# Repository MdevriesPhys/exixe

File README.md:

# exixe: Low-cost miniature Nixie tube driver modules

[Get exixe](https://www.tindie.com/products/dekuNukem/exixe-miniture-nixie-tube-driver-modules/) | [User manual](getting_started.md)

Forked from original dekuNukem repo, some modifications to boards and firmware.

exixe is a miniature driver module for IN-12 and IN-14 Nixie tubes.

It aims to simplify Nixie tube related projects by eliminating the need for obscure vintage driver chips and multiplexing circuits. Instead, you can control every digit and the RGB backlight via SPI using only 3 wires and 1 line of code.

exixe is cheap, small and modular for easy integration. It is compatible with Arduino, Raspberry Pi, and virtually all embedded dev boards today.

## Updated firmware 2026-03-03
Original firmware for IN-14 boards had an issue where the LEDs would be slightly on when set to 0 brightness. This has been updating in exixie14.hex firmware. See [Getting started](getting_started.md) for information about reflashing.

## Buy exixe on Tindie!

I did a small production run of exixe modules, and now you can buy them directly on Tindie:

https://www.tindie.com/products/dekuNukem/exixe-miniture-nixie-tube-driver-modules/

## Features

Compared to the traditional approach, exixe modules offers significant advantages:

#### Small and modular
* 2x4 cm (0.79x1.57 inches)
* Breadboard friendly
* Easy integration
* Reusable

#### SPI interface
* High speed, up to 24MHz SCLK
* Simple 16-byte command packet
* Available on virtually all embedded systems including Arduino and Raspberry Pi

#### Advanced control
* RGB backlight
* 128 brightness levels
* Hardware PWM on all cathodes and LEDs for smooth dimming and animations

#### Tube overdrive
* Optionally allows twice the cathode current
* For poisoned cathodes in second-hand tubes
* [Before](resources/no_overdrive.jpg) and [after](resources/with_overdrive.jpg).

#### No multiplexing
* Brighter display
* Longer tube life
* Simpler design
* Lower power consumption

## Getting started

Please see [getting_started.md](/getting_started.md)

## Arduino Library

Please [click here](arduino_library)

## Raspberry Pi/Python Library

Please [click here](python_library)

## Pinout, SPI command format and technical details

Please see [technical_details.md](/technical_details.md)

## Supported tubes

exixe-14 module is primarily designed for IN-14 Nixie tubes, but will also work with IN-16 and IN-19 tubes. IN-19 specific board in development.

exixe-12 module is primarily designed for IN-12 Nixie tubes, but works with IN-15 tubes as well.

## Using other tubes

You can also use exixe module with unsupported tubes, with some modification.

Please see [unsupported_tubes.md](/unsupported_tubes.md)

## Making some yourself

Please see [making_some.md](/making_some.md)

## Contact

Questions? Feel free to [open an issue](https://github.com/dekuNukem/exixe/issues). This is the preferred way since it helps other people too.

You can also email me at `dekunukem gmail com` for inquires.

## More photos

exixe-12 working with an Arduino Micro, showing a smooth crossfade animation:

exixe-14 in action on a [finished clock](https://github.com/dekuNukem/exixe_clock):

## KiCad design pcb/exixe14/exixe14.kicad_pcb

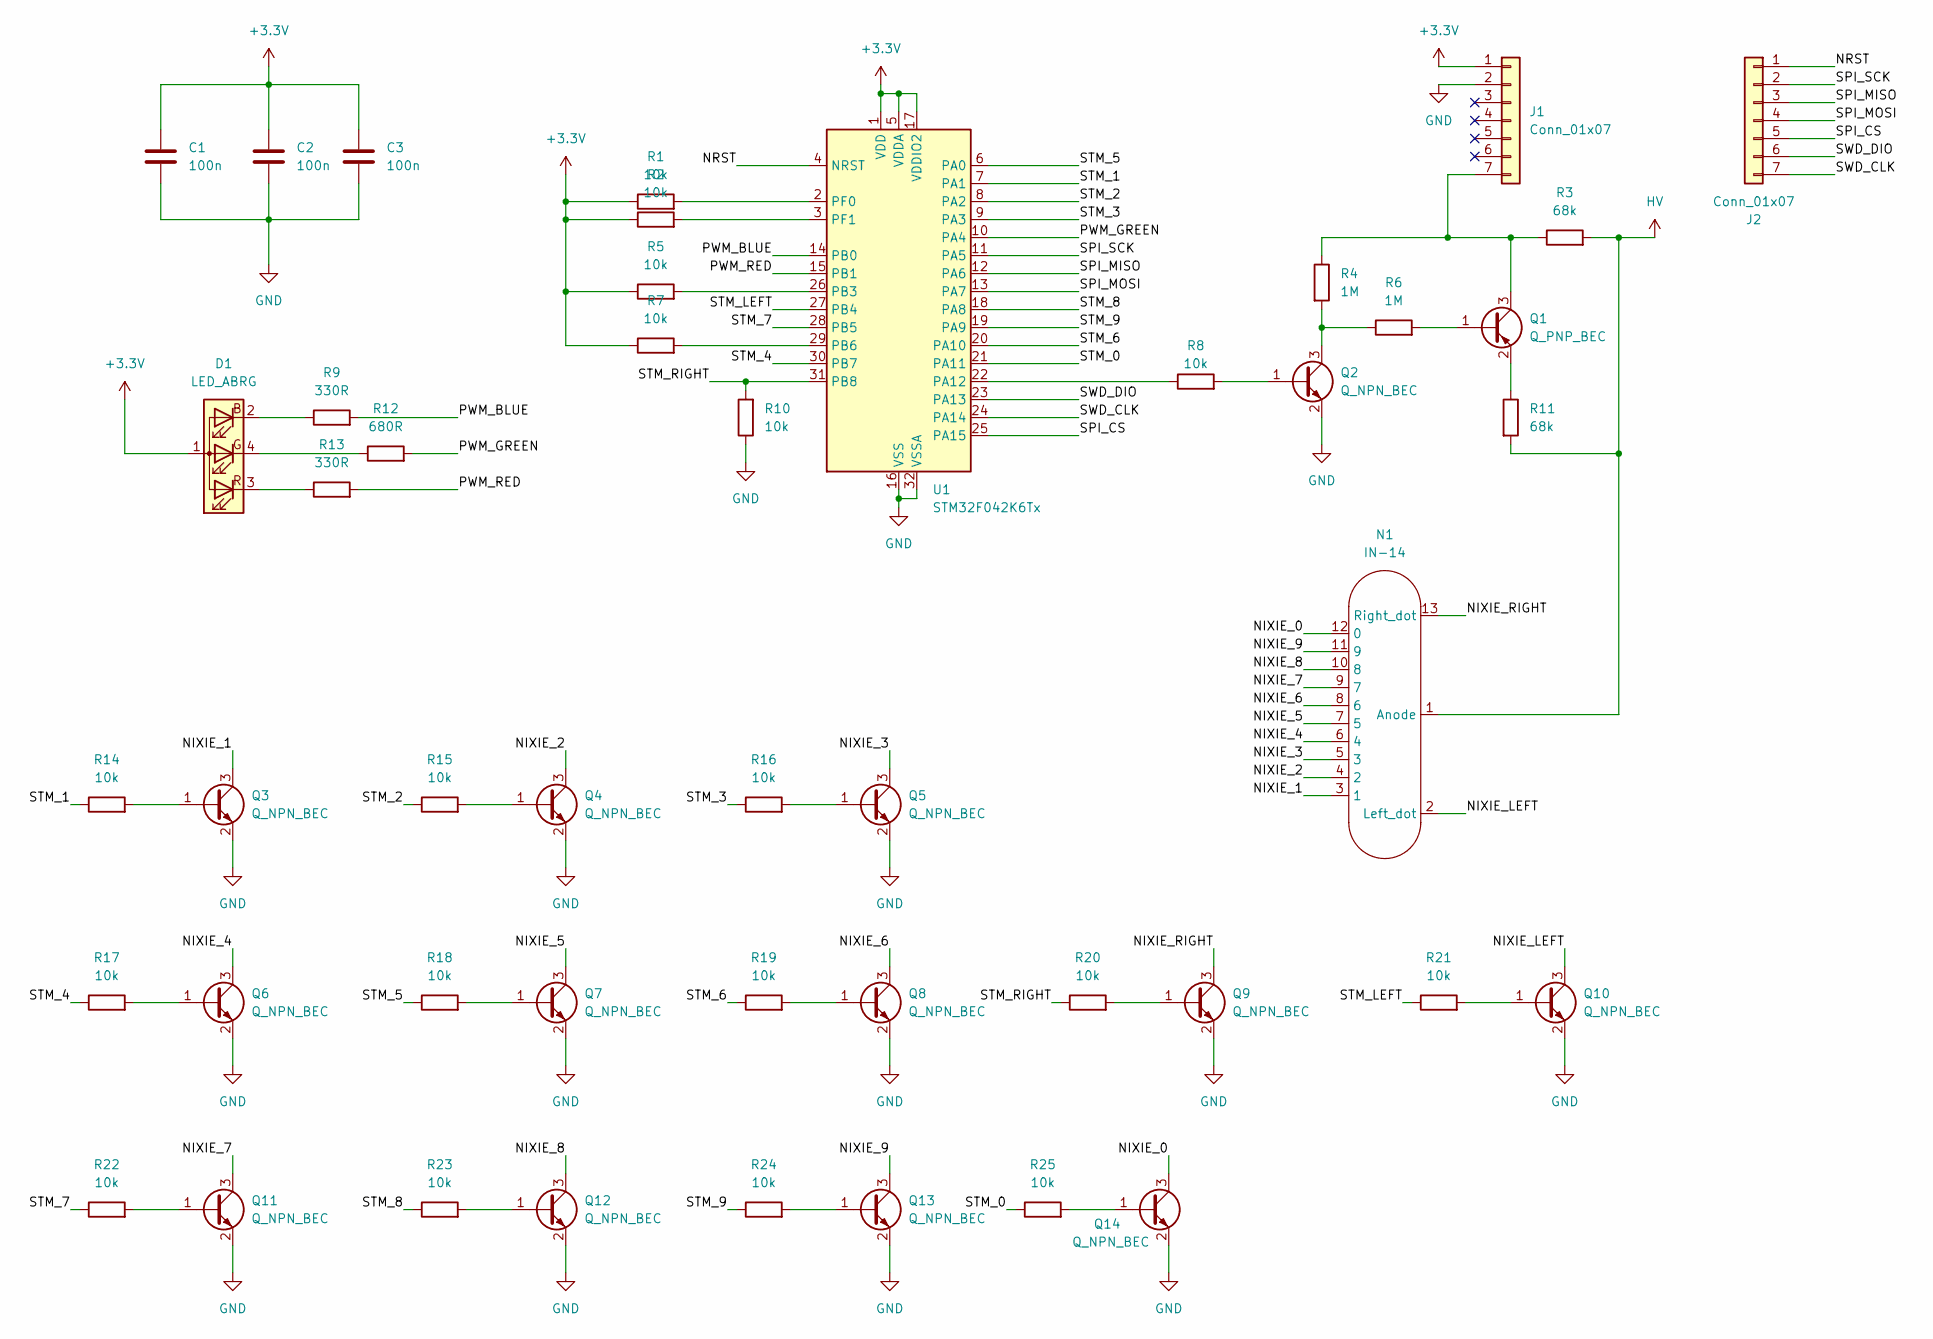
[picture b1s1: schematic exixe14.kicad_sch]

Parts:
C1, C2, C3: 100n; C_0805_2012Metric
D1: LED_ABRG; LED_RGB_Wuerth-PLCC4_3.2x2.8mm_150141M173100
J1, J2: Conn_01x07; PinHeader_1x07_P2.54mm_Vertical
N1: IN-14
Q1: Q_PNP_BEC; SOT-323_SC-70
Q2, Q3, Q4, Q5, Q6, Q7, Q8, Q9, Q10, Q11, Q12, Q13, Q14: Q_NPN_BEC; SOT-323_SC-70
R1, R2, R5, R7, R8, R10, R14, R15, R16, R17, R18, R19, R20, R21, R22, R23, R24, R25: 10k; R_0805_2012Metric
R3, R11: 68k; R_0805_2012Metric
R4, R6: 1M; R_0805_2012Metric
R9, R13: 330R; R_0805_2012Metric
R12: 680R; R_0805_2012Metric
U1: STM32F042K6Tx; LQFP-32_7x7mm_P0.8mm

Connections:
+3.3V: C1.1, C2.1, C3.1, D1.1 (A), J1.1, R1.1, R2.1, R5.1, R7.1, U1.1 (VDD), U1.5 (VDDA), U1.17 (VDDIO2)
/NIXIE_0: N1.12 (0), Q14.3 (C)
/NIXIE_1: N1.3 (1), Q3.3 (C)
/NIXIE_2: N1.4 (2), Q4.3 (C)
/NIXIE_3: N1.5 (3), Q5.3 (C)
/NIXIE_4: N1.6 (4), Q6.3 (C)
/NIXIE_5: N1.7 (5), Q7.3 (C)
/NIXIE_6: N1.8 (6), Q8.3 (C)
/NIXIE_7: N1.9 (7), Q11.3 (C)
/NIXIE_8: N1.10 (8), Q12.3 (C)
/NIXIE_9: N1.11 (9), Q13.3 (C)
/NIXIE_LEFT: N1.2 (Left_dot), Q10.3 (C)
/NIXIE_RIGHT: N1.13 (Right_dot), Q9.3 (C)
/NRST: J2.1, U1.4 (NRST)
/PWM_BLUE: R9.2, U1.14 (PB0)
/PWM_GREEN: R12.2, U1.10 (PA4)
/PWM_RED: R13.2, U1.15 (PB1)
/SPI_CS: J2.5, U1.25 (PA15)
/SPI_MISO: J2.3, U1.12 (PA6)
/SPI_MOSI: J2.4, U1.13 (PA7)
/SPI_SCK: J2.2, U1.11 (PA5)
/STM_0: R25.1, U1.21 (PA11)
/STM_1: R14.1, U1.7 (PA1)
/STM_2: R15.1, U1.8 (PA2)
/STM_3: R16.1, U1.9 (PA3)
/STM_4: R17.1, U1.30 (PB7)
/STM_5: R18.1, U1.6 (PA0)
/STM_6: R19.1, U1.20 (PA10)
/STM_7: R22.1, U1.28 (PB5)
/STM_8: R23.1, U1.18 (PA8)
/STM_9: R24.1, U1.19 (PA9)
/STM_LEFT: R21.1, U1.27 (PB4)
/STM_RIGHT: R10.2, R20.1, U1.31 (PB8)
/SWD_CLK: J2.7, U1.24 (PA14)
/SWD_DIO: J2.6, U1.23 (PA13)
GND: C1.2, C2.2, C3.2, J1.2, Q2.2 (E), Q3.2 (E), Q4.2 (E), Q5.2 (E), Q6.2 (E), Q7.2 (E), Q8.2 (E), Q9.2 (E), Q10.2 (E), Q11.2 (E), Q12.2 (E), Q13.2 (E), Q14.2 (E), R10.1, U1.16 (VSS), U1.32 (VSSA)
HV: N1.1 (Anode), R3.2, R11.2
unnamed: D1.2 (BK), R9.1
unnamed: D1.4 (GK), R12.1
unnamed: D1.3 (RK), R13.1
unnamed: J1.7, Q1.3 (C), R3.1, R4.1
unnamed: Q1.1 (B), R6.2
unnamed: Q1.2 (E), R11.1
unnamed: Q2.1 (B), R8.2
unnamed: Q2.3 (C), R4.2, R6.1
unnamed: Q3.1 (B), R14.2
unnamed: Q4.1 (B), R15.2
unnamed: Q5.1 (B), R16.2
unnamed: Q6.1 (B), R17.2
unnamed: Q7.1 (B), R18.2
unnamed: Q8.1 (B), R19.2
unnamed: Q9.1 (B), R20.2
unnamed: Q10.1 (B), R21.2
unnamed: Q11.1 (B), R22.2
unnamed: Q12.1 (B), R23.2
unnamed: Q13.1 (B), R24.2
unnamed: Q14.1 (B), R25.2
unnamed: R8.1, U1.22 (PA12)
unnamed: R5.2, U1.26 (PB3)
unnamed: R7.2, U1.29 (PB6)
unnamed: R1.2, U1.2 (PF0)
unnamed: R2.2, U1.3 (PF1)

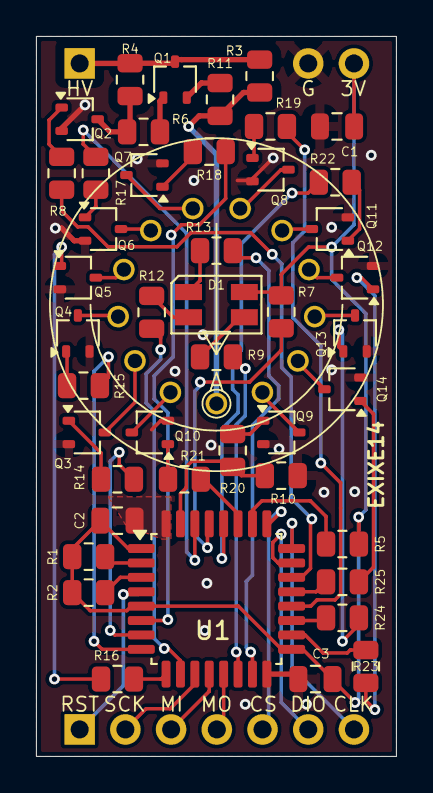
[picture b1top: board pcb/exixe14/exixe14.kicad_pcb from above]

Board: 2 copper layers, 20.0 x 40.0 mm, 47 parts (0 on the bottom side), 62 nets.

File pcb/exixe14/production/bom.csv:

Designator,Footprint,Quantity,Value,LCSC Part #
"C1, C2, C3",0805,3,100n,
D1,LED_RGB_Wuerth-PLCC4_3.2x2.8mm_150141M173100,1,LED_ABRG,
"J1, J2",PinHeader_1x07_P2.54mm_Vertical,2,Conn_01x07,
N1,IN-14,1,IN-14,
Q1,SOT-323_SC-70,1,Q_PNP_BEC,
"Q10, Q11, Q12, Q13, Q14, Q2, Q3, Q4, Q5, Q6, Q7, Q8, Q9",SOT-323_SC-70,13,Q_NPN_BEC,
"R1, R10, R14, R15, R16, R17, R18, R19, R2, R20, R21, R22, R23, R24, R25, R5, R7, R8",0805,18,10k,
"R11, R3",0805,2,68k,
R12,0805,1,680R,
"R13, R9",0805,2,330R,
"R4, R6",0805,2,1M,
U1,LQFP-32_7x7mm_P0.8mm,1,STM32F042K6Tx,

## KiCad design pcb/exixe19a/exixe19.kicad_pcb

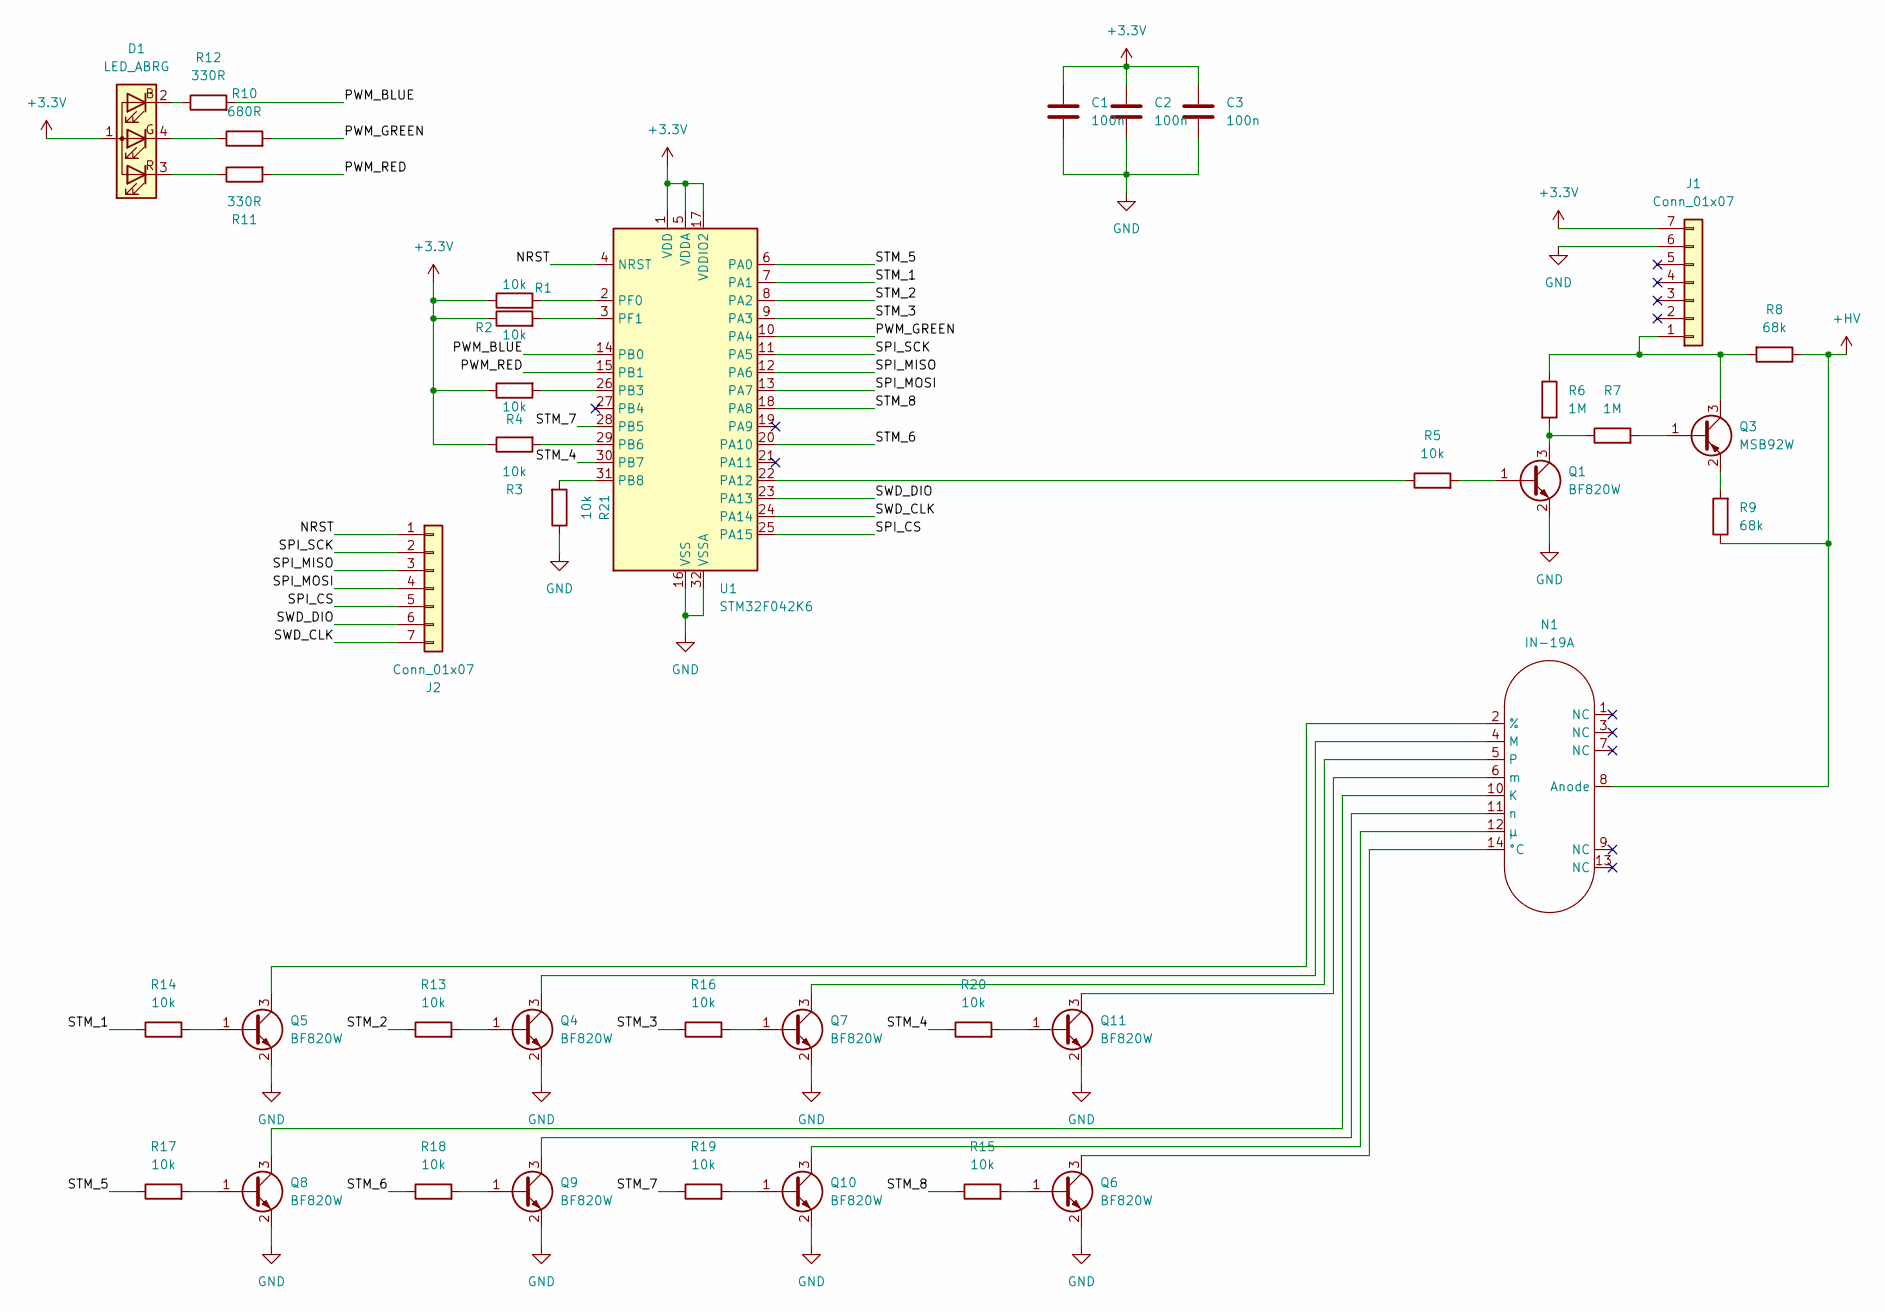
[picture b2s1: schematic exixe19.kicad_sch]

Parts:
C1, C2, C3: 100n; C_0805_2012Metric
D1: LED_ABRG; LED_RGB_Wuerth-PLCC4_3.2x2.8mm_150141M173100
J1: Conn_01x07; PinHeader_1x07_P2.54mm_Vertical_special
J2: Conn_01x07; PinHeader_1x07_P2.54mm_Vertical
N1: IN-19A
Q1, Q4, Q5, Q6, Q7, Q8, Q9, Q10, Q11: BF820W; SOT-323_SC-70
Q3: MSB92W; SOT-323_SC-70
R1, R2, R3, R4, R5, R13, R14, R15, R16, R17, R18, R19, R20, R21: 10k; R_0805_2012Metric
R6, R7: 1M; R_0805_2012Metric
R8, R9: 68k; R_0805_2012Metric
R10: 680R; R_0805_2012Metric
R11, R12: 330R; R_0805_2012Metric
U1: STM32F042K6; TQFP-32_7x7mm_P0.8mm

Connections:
+3.3V: C1.1, C2.1, C3.1, D1.1 (A), J1.7, R1.1, R2.1, R3.1, R4.1, U1.1 (VDD), U1.5 (VDDA), U1.17 (VDDIO2)
+HV: N1.8 (Anode), R8.1, R9.1
/NRST: J2.1, U1.4 (NRST)
/PWM_BLUE: R12.2, U1.14 (PB0)
/PWM_GREEN: R10.2, U1.10 (PA4)
/PWM_RED: R11.2, U1.15 (PB1)
/SPI_CS: J2.5, U1.25 (PA15)
/SPI_MISO: J2.3, U1.12 (PA6)
/SPI_MOSI: J2.4, U1.13 (PA7)
/SPI_SCK: J2.2, U1.11 (PA5)
/STM_1: R14.1, U1.7 (PA1)
/STM_2: R13.1, U1.8 (PA2)
/STM_3: R16.1, U1.9 (PA3)
/STM_4: R20.1, U1.30 (PB7)
/STM_5: R17.1, U1.6 (PA0)
/STM_6: R18.1, U1.20 (PA10)
/STM_7: R19.1, U1.28 (PB5)
/STM_8: R15.1, U1.18 (PA8)
/SWD_CLK: J2.7, U1.24 (PA14)
/SWD_DIO: J2.6, U1.23 (PA13)
GND: C1.2, C2.2, C3.2, J1.6, Q1.2 (E), Q4.2 (E), Q5.2 (E), Q6.2 (E), Q7.2 (E), Q8.2 (E), Q9.2 (E), Q10.2 (E), Q11.2 (E), R21.1, U1.16 (VSS), U1.32 (VSSA)
unnamed: D1.2 (BK), R12.1
unnamed: D1.4 (GK), R10.1
unnamed: D1.3 (RK), R11.1
unnamed: J1.1, Q3.3 (C), R6.1, R8.2
unnamed: N1.2 (%), Q5.3 (C)
unnamed: N1.10 (K), Q8.3 (C)
unnamed: N1.4 (M), Q4.3 (C)
unnamed: N1.5, Q7.3 (C)
unnamed: N1.6 (m), Q11.3 (C)
unnamed: N1.11 (n), Q9.3 (C)
unnamed: N1.14 (°С), Q6.3 (C)
unnamed: N1.12 (µ), Q10.3 (C)
unnamed: Q1.1 (B), R5.2
unnamed: Q1.3 (C), R6.2, R7.1
unnamed: Q3.1 (B), R7.2
unnamed: Q3.2 (E), R9.2
unnamed: Q4.1 (B), R13.2
unnamed: Q5.1 (B), R14.2
unnamed: Q6.1 (B), R15.2
unnamed: Q7.1 (B), R16.2
unnamed: Q8.1 (B), R17.2
unnamed: Q9.1 (B), R18.2
unnamed: Q10.1 (B), R19.2
unnamed: Q11.1 (B), R20.2
unnamed: R5.1, U1.22 (PA12)
unnamed: R4.2, U1.26 (PB3)
unnamed: R3.2, U1.29 (PB6)
unnamed: R21.2, U1.31 (PB8)
unnamed: R1.2, U1.2 (PF0)
unnamed: R2.2, U1.3 (PF1)

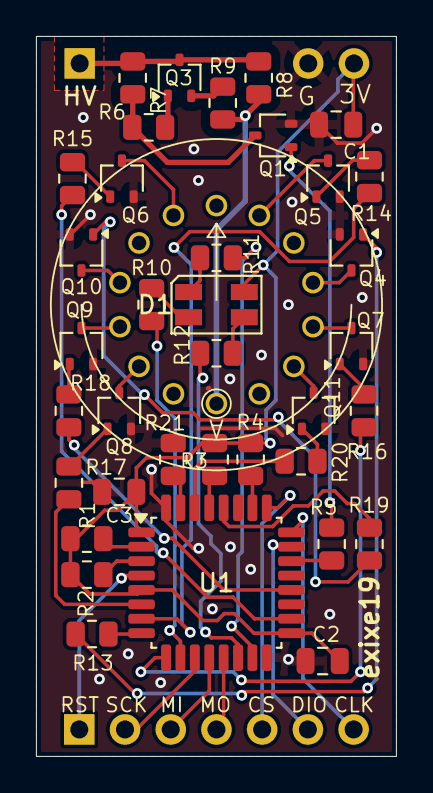
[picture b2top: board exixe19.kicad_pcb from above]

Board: 2 copper layers, 20.0 x 40.0 mm, 39 parts (0 on the bottom side), 51 nets.

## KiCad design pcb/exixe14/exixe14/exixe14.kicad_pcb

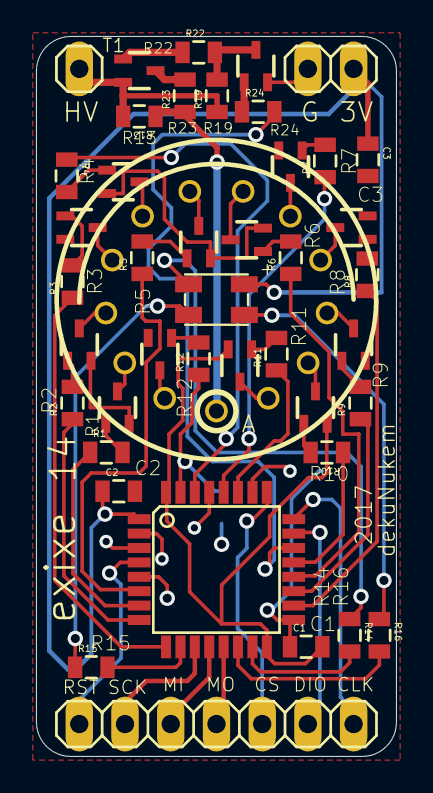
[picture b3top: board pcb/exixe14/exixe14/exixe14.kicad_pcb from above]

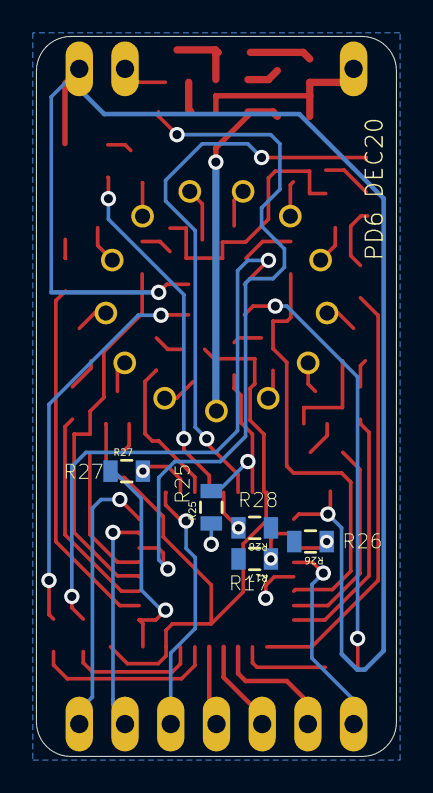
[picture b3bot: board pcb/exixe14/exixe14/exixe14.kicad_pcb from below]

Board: 16 copper layers, 20.0 x 40.0 mm, 47 parts (5 on the bottom side), 62 nets.

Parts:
C1, C2, C3: 100nF; 0805
D1: RGB_LED_CA-150141M173100-R&G&B; 3528-COMMON-ANODE
IC1: STM32F042K6; TQFP32-08
JP1, JP2: 1X07
N1: IN-14
Q1, Q2, Q3, Q4, Q5, Q6, Q7, Q8, Q9, Q10, Q11, Q12, Q13: SOT323
R1, R2, R3, R4, R5, R6, R7, R8, R9, R10, R11, R12, R17, R24, R25, R26, R27, R28: 10K; 0805
R13, R23: 68K; 0805
R14, R16: 330; 0805
R15: 680; 0805
R19, R22: 1M; 0805
T1: SOT323

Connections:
+3V3: C1.1, C2.1, C3.1, D1.1, IC1.1, IC1.5, IC1.17, JP1.7, R17.2, R26.2, R27.1, R28.1
+180V: N1.A, R13.1, R23.1
BAKE: IC1.22, R24.2
GND: C1.2, C2.2, C3.2, IC1.16, IC1.32, JP1.6, Q1.2, Q2.2, Q3.2, Q4.2, Q5.2, Q6.2, Q7.2, Q8.2, Q9.2, Q10.2, Q11.2, Q12.2, Q13.2, R25.1
unnamed: Q1.1, R1.2
unnamed: IC1.2, R17.1
unnamed: D1.4, R15.1
unnamed: Q2.1, R2.2
unnamed: Q3.1, R3.2
unnamed: Q4.1, R4.2
unnamed: Q5.1, R5.2
unnamed: Q6.1, R6.2
unnamed: Q7.1, R7.2
unnamed: Q8.1, R8.2
unnamed: Q9.1, R9.2
unnamed: Q10.1, R10.2
unnamed: Q11.1, R11.2
unnamed: Q12.1, R12.2
unnamed: D1.3, R14.1
unnamed: IC1.3, R26.1
unnamed: JP1.1, R13.2, R19.1, T1.3
unnamed: R22.1, T1.2
unnamed: D1.2, R16.1
unnamed: Q13.3, R19.2, R22.2
unnamed: Q13.1, R24.1
unnamed: R23.2, T1.1
unnamed: IC1.26, R27.2
NIXIE_1: N1.1, Q1.3
NIXIE_2: N1.2, Q2.3
NIXIE_3: N1.3, Q3.3
NIXIE_4: N1.4, Q4.3
NIXIE_5: N1.5, Q5.3
NIXIE_6: N1.6, Q6.3
NIXIE_7: N1.7, Q7.3
NIXIE_8: N1.8, Q8.3
NIXIE_9: N1.9, Q9.3
NIXIE_10: N1.0, Q10.3
NIXIE_DOT_LEFT: N1.LHDP, Q11.3
NIXIE_DOT_RIGHT: N1.RHDP, Q12.3
NRST: IC1.4, JP2.1
PWM_BLUE: IC1.14, R16.2
PWM_GREEN: IC1.10, R15.2
PWM_RED: IC1.15, R14.2
SPI_CS: IC1.25, JP2.5
SPI_MISO: IC1.12, JP2.3
SPI_MOSI: IC1.13, JP2.4
SPI_SCK: IC1.11, JP2.2
STM_1: IC1.7, R1.1
STM_2: IC1.8, R2.1
STM_3: IC1.9, R3.1
STM_4: IC1.30, R4.1
STM_5: IC1.6, R5.1
STM_6: IC1.20, R6.1
STM_7: IC1.28, R7.1
STM_8: IC1.18, R8.1
STM_9: IC1.19, R9.1
STM_10: IC1.21, R10.1
STM_DOT_LEFT: IC1.27, R11.1
STM_DOT_RIGHT: IC1.31, R12.1, R25.2
SWD_CLK: IC1.24, JP2.7
SWD_DIO: IC1.23, JP2.6
UART_TX: IC1.29, R28.2

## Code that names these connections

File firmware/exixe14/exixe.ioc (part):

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Mcu.Name=STM32F042K(4-6)Tx
Mcu.Package=LQFP32
Mcu.UserName=STM32F042K6Tx
PA0.Signal=S_TIM2_CH1_ETR
PA1.Signal=S_TIM2_CH2
PA10.Signal=S_TIM1_CH3
PA11.Signal=S_TIM1_CH4
PA12.GPIOParameters=GPIO_PuPd,GPIO_Label
PA12.GPIO_Label=BAKE
PA12.GPIO_PuPd=GPIO_NOPULL
PA12.Signal=GPIO_Output
PA13.Mode=Serial_Wire
PA13.Signal=SYS_SWDIO
PA14.Mode=Serial_Wire
PA14.Signal=SYS_SWCLK
PA15.Mode=NSS_Signal_Hard_Input
PA15.Signal=SPI1_NSS
PA2.Signal=S_TIM2_CH3
PA3.Signal=S_TIM2_CH4
PA4.Signal=S_TIM14_CH1
PA5.Mode=Full_Duplex_Slave
PA5.Signal=SPI1_SCK
PA6.Mode=Full_Duplex_Slave
PA6.Signal=SPI1_MISO
PA7.Mode=Full_Duplex_Slave
PA7.Signal=SPI1_MOSI
PA8.Signal=S_TIM1_CH1
PA9.Signal=S_TIM1_CH2
PB0.Signal=S_TIM3_CH3
PB1.Signal=S_TIM3_CH4
PB4.Signal=S_TIM3_CH1
PB5.Signal=S_TIM3_CH2
PB6.Mode=Half_duplex(single_wire_mode)
PB6.Signal=USART1_TX
PB7.Mode=PWM Generation1 CH1N
PB7.Signal=TIM17_CH1N
PB8.Signal=S_TIM16_CH1
RCC.SYSCLKFreq_VALUE=48000000
RCC.SYSCLKSource=RCC_SYSCLKSOURCE_HSI48
board=exixe

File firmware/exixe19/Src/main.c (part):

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  __HAL_RCC_GPIOB_CLK_ENABLE();

  /*Configure GPIO pin Output Level */
  HAL_GPIO_WritePin(BAKE_GPIO_Port, BAKE_Pin, GPIO_PIN_RESET);

  /*Configure GPIO pins : PF0 PF1 */
  GPIO_InitStruct.Pin = GPIO_PIN_0|GPIO_PIN_1;
  GPIO_InitStruct.Mode = GPIO_MODE_ANALOG;
  GPIO_InitStruct.Pull = GPIO_NOPULL;
  HAL_GPIO_Init(GPIOF, &GPIO_InitStruct);

  /*Configure GPIO pins : PA9 PA11 */
  GPIO_InitStruct.Pin = GPIO_PIN_9|GPIO_PIN_11;
  GPIO_InitStruct.Mode = GPIO_MODE_ANALOG;
  GPIO_InitStruct.Pull = GPIO_NOPULL;
  HAL_GPIO_Init(GPIOA, &GPIO_InitStruct);

  /*Configure GPIO pin : BAKE_Pin */
  GPIO_InitStruct.Pin = BAKE_Pin;
  GPIO_InitStruct.Mode = GPIO_MODE_OUTPUT_PP;
  GPIO_InitStruct.Pull = GPIO_NOPULL;
  GPIO_InitStruct.Speed = GPIO_SPEED_FREQ_LOW;
  HAL_GPIO_Init(BAKE_GPIO_Port, &GPIO_InitStruct);

  /*Configure GPIO pins : PB3 PB4 */
  GPIO_InitStruct.Pin = GPIO_PIN_3|GPIO_PIN_4;
  GPIO_InitStruct.Mode = GPIO_MODE_ANALOG;
  GPIO_InitStruct.Pull = GPIO_NOPULL;
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    HAL_NVIC_SystemReset();
  set_pwm(spi_recv_buf);
  if(spi_recv_buf[0] & 0x1)
      HAL_GPIO_WritePin(BAKE_GPIO_Port, BAKE_Pin, GPIO_PIN_SET);
  else
      HAL_GPIO_WritePin(BAKE_GPIO_Port, BAKE_Pin, GPIO_PIN_RESET);
  HAL_SPI_Receive_DMA(&hspi1, spi_recv_buf, SPI_BUF_SIZE);
}

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
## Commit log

2025-10-02 IN-19A PCB design started
2025-10-14 pcb design for IN-19 tubes
2025-10-15 updated exixe19a pcb
2025-10-28 trying to do firmware
2026-01-09 Turns out I need to watch out for grounding planes that aren't actually connected to anything
2026-01-09 new version should work
2026-01-13 updated layout, made new version of exixe14 schematic
2026-01-15 Tidied up IN-19, started update to IN-14 board
2026-01-27 updating exixe14 pcb
2026-02-01 pcb layout is hard
2026-02-18 working on exixe14 pcb
2026-02-18 layout is hard
2026-02-20 This layout looks okay?
2026-03-01 attempt to correct firmware to remove glowing led issue
2026-03-02 LED fix check, helps if I actually make the .hex...
2026-03-03 Update to exixie14 firmware, the LEDs will now be off when set to (0,0,0)

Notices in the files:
firmware/exixe19/Src/main.c:
Copyright (c) 2025 STMicroelectronics.
All rights reserved.
This software is licensed under terms that can be found in the LICENSE file
